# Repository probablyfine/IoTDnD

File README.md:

# IoTDnD
an internet-of-things Do Not Disturb light

# What/Why
This is a small WiFi device that hangs out on your network and serves up a web interface to your browser. You use the web interface to turn a light on the device on and off.

This one was a request from a friend. He and his roommate were both working from home, and they wanted to be able to quickly and easily let each other know when one was on a work call. I initially suggested using a text message, but eventually I sent them two of these little boxes:

Tap the sun for on, tap the moon for off.

# How
There are a few parts to this project.
- An [ESP32](https://en.wikipedia.org/wiki/ESP32)-based [module from Adafruit](https://www.adafruit.com/product/4201), which handles the WiFi functions
- An [M4](https://en.wikipedia.org/wiki/ARM_Cortex-M)-based [microcontroller board from Adafruit](https://www.adafruit.com/product/3800), which controls the WiFi module over [SPI](https://en.wikipedia.org/wiki/Serial_Peripheral_Interface), and controls the device's LED
- A [custom-made](https://github.com/probablyfine/IoTDnD/raw/main/photos/EAGLE-brd.png) [PCB](https://github.com/probablyfine/IoTDnD/raw/main/photos/IMG_6150.jpg) that connects the microcontroller to the WiFi module and to the LED, and provides a way to mount everything in a box
- Some [Python code](https://github.com/probablyfine/IoTDnD/blob/main/code/code.py) that runs a web server on the microcontroller
- A [web-based interface](https://github.com/probablyfine/IoTDnD/blob/main/code/index.html) that the microcontroller sends to your browser via the WiFi module

# Details
## Hardware
### Smart parts
The critical components are the [microcontroller](https://www.adafruit.com/product/3800) and the [WiFi module](https://www.adafruit.com/product/4201). There are plenty of similar solutions out there, but this pairing works very well. If you're putting this together yourself, you probably want [this board](https://www.adafruit.com/product/4000) from Adafruit instead, which has both of these products built onto it-- no need to worry about soldering anything. I wanted to use a particular [enclosure](https://www.aliexpress.com/item/32782067140.html) that was too small for the single-board option, and I liked having an excuse to make a PCB, so I got the two components separately. If you go that route there's good [documentation](https://learn.adafruit.com/adafruit-airlift-breakout/overview) from Adafruit.

The last important part is the LED. Both of the Adafruit microcontroller boards I linked have on-board RGB LEDs, which are very bright and totally usable. I used these [nice 5mm ones](https://www.pololu.com/product/2535) from Pololu instead-- they have a diffused lens, which is easier on the eyes, and the form-factor makes it easy to display outside the enclosure.

### Dumb parts
I laid out the PCB in the free version of [EAGLE](https://en.wikipedia.org/wiki/EAGLE_(program)). There are very good arguments for using [KiCad](https://en.wikipedia.org/wiki/KiCad) instead, but EAGLE is what I know. Plus, it's what Adafruit uses, which means I was able to import their board files and use the two modules' footprints for my layout. 

The PCB is very simple. There are places to mount the microcontroller and the WiFi module, the RGB LED, and two capacitors (I only ended up having room for one in the enclosure). There's a mounting hole that lines up with the enclosure's internal screw hole, and cutouts to make room for the screw holes for the enclosure's cover.

The copper traces are pretty minimal, too. There are a few power connections, some connections between the microcontroller and WiFi module, and a data line from the microcontroller to the RGB LED.

Getting professional-quality PCBs made is insanely easy and inexpensive these days. I normally use [OSH Park](https://oshpark.com/) and highly recommend them. For this project, I wanted to try out [JLCPCB](https://jlcpcb.com/), and had a good experience with them as well. One nice feature of OSH Park's service is that you can drop an [EAGLE .brd file](https://github.com/probablyfine/IoTDnD/blob/main/pcb/IoTDnD.brd) directly onto their landing page without generating [Gerber files](https://en.wikipedia.org/wiki/Gerber_format) first.

With everything soldered, I used a Dremel tool to bore out a hole in the enclosure for the LED and a cutout for the USB port for power.

#### 
## Software
The microcontroller I'm using runs [CircuitPython](https://circuitpython.org/), which makes it possible to do some pretty powerful things with very little code. Adafruit also provides a ton of libraries and examples; I based the web server functionality in my code on [this example](https://github.com/adafruit/Adafruit_CircuitPython_ESP32SPI/blob/master/examples/server/esp32spi_wsgiserver.py) they provide.

The [code](https://github.com/probablyfine/IoTDnD/blob/main/code/code.py) does a few things:
- sets up an SPI connection with the WiFi module
- connects to a WiFi network (2.4 GHz only) using the specified [SSID and password](https://github.com/probablyfine/IoTDnD/blob/main/code/secrets.py)
- Polls the WiFi module for incoming [HTTP requests](https://developer.mozilla.org/en-US/docs/Web/HTTP/Methods)

It responds to a GET request to its root IP address by returning an [HTML file](https://github.com/probablyfine/IoTDnD/blob/main/code/index.html). It also reponds to PUT requests to '/light_on' and '/light_off' by turning the LED on or off.

You can see how the browser renders the HTML file in the image towards the top of this document. That file is a heavily modified version of [this example code](https://github.com/cyborg5/IRLib2/blob/master/IRLib2/examples/Iot_IR/adafruit_remote.html) that Chris Young did for Adafruit. Basically, it renders two buttons and a small status indicator (the little octopus in the upper left of the screenshot above). Tapping either of the two buttons generates the appropriate PUT request, which is received by the WiFi module and microcontroller.

If you're trying this out, you need to modify [this line](https://github.com/probablyfine/IoTDnD/blob/7540f51e6421b3274a6c39247116161634d67c39/code/index.html#L48) in the HTML document to match the IP address of the WiFi module. If this is a permanent installation, you'll want to configure your router to assign the module a static IP address so you don't have to update the HTML file on re-connects.

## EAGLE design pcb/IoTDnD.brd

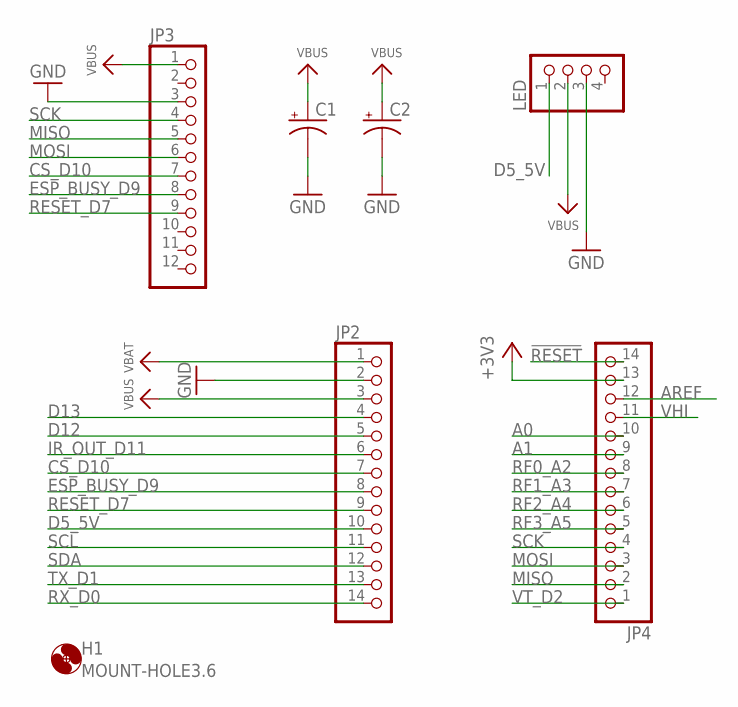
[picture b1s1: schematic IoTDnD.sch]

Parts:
C1, C2: CPOL-USE2.5-6; E2,5-6
H1: MOUNT-HOLE3.6; 3,6
JP2, JP4: HEADER-1X14; 1X14_ROUND70
JP3: HEADER-1X12; 1X12_ROUND
LED: PINHD-1X4; 1X04

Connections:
!RESET: JP4.14
+3V3: JP4.13
A0: JP4.10
A1: JP4.9
AREF: JP4.12
CS_D10: JP2.7, JP3.7
D5_5V: JP2.10, LED.1
D12: JP2.5
D13: JP2.4
ESP_BUSY_D9: JP2.8, JP3.8
GND: C1.-, C2.-, JP2.2, JP3.3, LED.3
IR_OUT_D11: JP2.6
MISO: JP3.5, JP4.2
MOSI: JP3.6, JP4.3
RESET_D7: JP2.9, JP3.9
RF0_A2: JP4.8
RF1_A3: JP4.7
RF2_A4: JP4.6
RF3_A5: JP4.5
RX_D0: JP2.14
SCK: JP3.4, JP4.4
SCL: JP2.11
SDA: JP2.12
TX_D1: JP2.13
VBAT: JP2.1
VBUS: C1.+, C2.+, JP2.3, JP3.1, LED.2
VHI: JP4.11
VT_D2: JP4.1

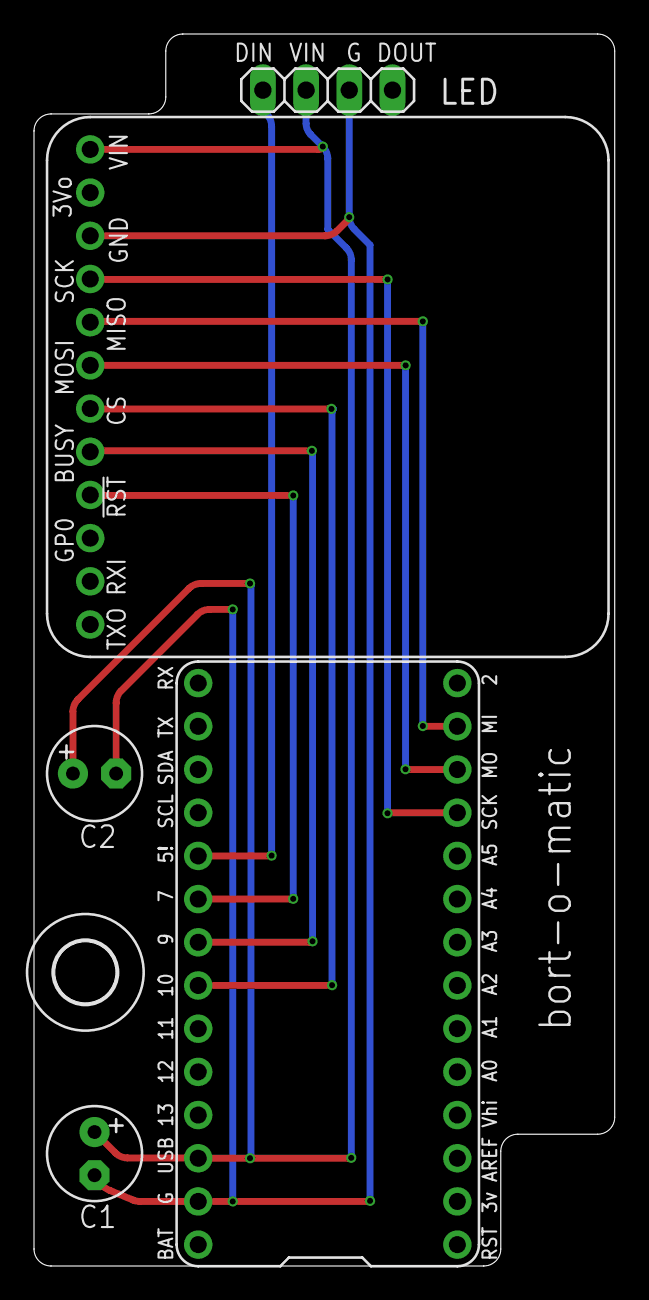
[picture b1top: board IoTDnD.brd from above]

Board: 2 copper layers, 34.1 x 72.5 mm, 9 parts (1 on the bottom side), 9 nets.

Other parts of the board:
U$4: ITSYM4_TOP
U$5: ITSYM4_BOT

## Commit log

2021-05-26 adjust photos
2021-05-27 add photo of web interface
2021-05-27 adjust photo
2021-05-28 add more photos
2021-05-28 adjust image
2021-05-28 adjust images

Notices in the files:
parts and their libraries:
microbuilder: This work is placed in the public domain, and may be freely used for commercial and non-commercial work with the following conditions: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
